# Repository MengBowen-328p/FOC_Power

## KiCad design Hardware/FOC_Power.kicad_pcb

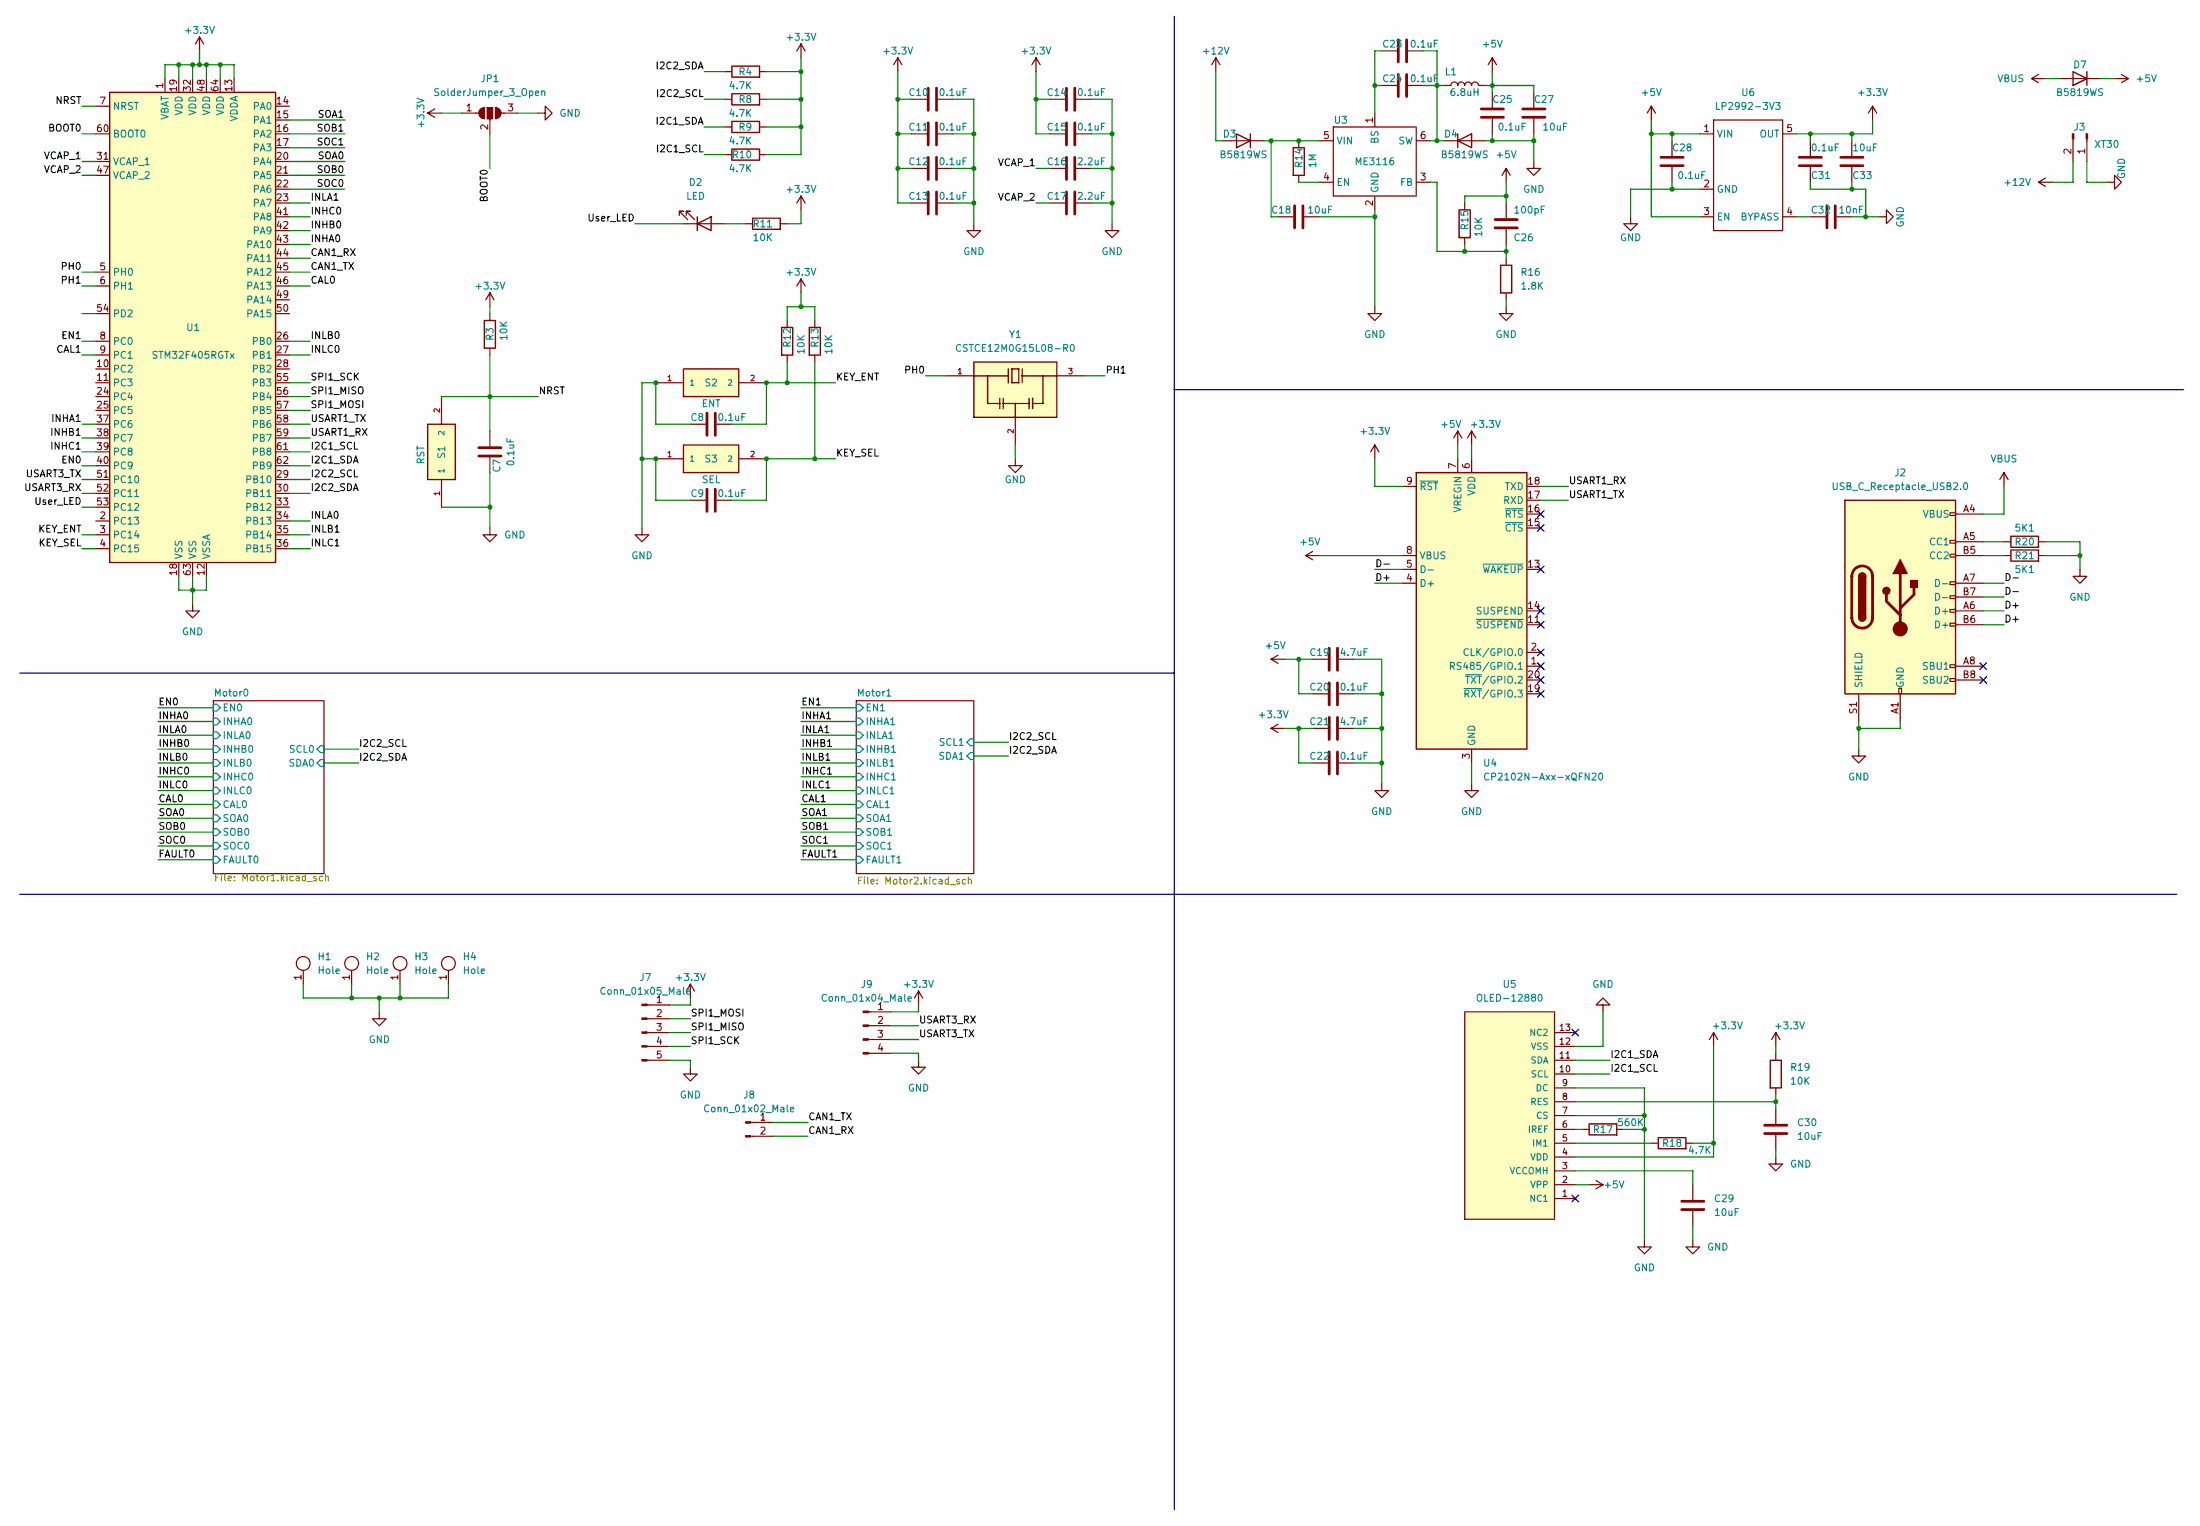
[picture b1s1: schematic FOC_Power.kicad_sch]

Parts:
C7, C8, C9, C10, C11, C12, C13, C14, C15, C20, C22, C23, C24, C25, C28, C31: 0.1uF; C_0402_1005Metric
C16, C17: 2.2uF; C_0402_1005Metric
C18, C27, C29, C30, C33: 10uF; C_0402_1005Metric
C19, C21: 4.7uF; C_0402_1005Metric
C26: 100pF; C_0402_1005Metric
C32: 10nF; C_0402_1005Metric
D2: LED; LED_0402_1005Metric
D3, D4, D7: B5819WS; D_SOD-323
H1, H2, H3, H4: Hole
J2: USB_C_Receptacle_USB2.0; USB_C_Receptacle_Palconn_UTC16-G
J3: XT30; XT30_SMD
J7: Conn_01x05_Male; JST_SUR_SM05B-SURS-TF_1x05-1MP_P0.80mm_Horizontal
J8: Conn_01x02_Male; JST_SUR_SM02B-SURS-TF_1x02-1MP_P0.80mm_Horizontal
J9: Conn_01x04_Male; JST_SUR_SM04B-SURS-TF_1x04-1MP_P0.80mm_Horizontal
JP1: SolderJumper_3_Open; SolderJumper-3_P1.3mm_Open_RoundedPad1.0x1.5mm
L1: 6.8uH; L_0805_2012Metric
R3, R11, R12, R13, R15, R19: 10K; R_0402_1005Metric
R4, R8, R9, R10, R18: 4.7K; R_0402_1005Metric
R14: 1M; R_0402_1005Metric
R16: 1.8K; R_0402_1005Metric
R17: 560K; R_0402_1005Metric
R20, R21: 5K1; R_0402_1005Metric
S1: RST; SKRK; Manufacturer_Part_Number SKRKAEE010
S2: ENT; SKRK; Manufacturer_Part_Number SKRKAEE010
S3: SEL; SKRK; Manufacturer_Part_Number SKRKAEE010
U1: STM32F405RGTx; LQFP-64_10x10mm_P0.5mm
U3: ME3116; SOT-23-6
U4: CP2102N-Axx-xQFN20; SiliconLabs_QFN-20-1EP_3x3mm_P0.5mm_EP1.8x1.8mm
U5: OLED-12880
U6: LP2992-3V3; SOT-23-5
Y1: CSTCE12M0G15L08-R0; OSC_CSTCE12M0G15L08-R0; PARTREV May 7, 2019

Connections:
+3V3: C10.2, C11.2, C12.2, C13.2, C14.2, C15.2, C21.1, C22.1, C31.1, C33.1, J7.1, J9.1, JP1.1 (A), R3.1, R4.2, R8.2, R9.2, R10.2, R11.2, R12.1, R13.1, R18.2, R19.1, U1.1 (VBAT), U1.13 (VDDA), U1.19 (VDD), U1.32 (VDD), U1.48 (VDD), U1.64 (VDD), U4.6 (VDD), U4.9 (~RST), U5.4 (VDD), U6.5 (OUT); also elsewhere on the board
+5V: C19.1, C20.1, C25.2, C26.1, C27.2, C28.2, D7.1 (K), L1.2, R15.1, U4.7 (VREGIN), U4.8 (VBUS), U5.2 (VPP), U6.1 (VIN), U6.3 (EN)
+12V: D3.2 (A), J3.2; also elsewhere on the board
/BOOT0: JP1.2 (C), U1.60 (BOOT0)
/CAL0: U1.46 (PA13); also elsewhere on the board
/CAL1: U1.9 (PC1); also elsewhere on the board
/CAN1_RX: J8.2, U1.44 (PA11)
/CAN1_TX: J8.1, U1.45 (PA12)
/D+: J2.A6 (D+), J2.B6 (D+), U4.4 (D+)
/D-: J2.A7 (D-), J2.B7 (D-), U4.5 (D-)
/EN0: U1.40 (PC9); also elsewhere on the board
/EN1: U1.8 (PC0); also elsewhere on the board
/I2C1_SCL: R10.1, U1.61 (PB8), U5.10 (SCL)
/I2C1_SDA: R9.1, U1.62 (PB9), U5.11 (SDA)
/I2C2_SCL: R8.1, U1.29 (PB10); also elsewhere on the board
/I2C2_SDA: R4.1, U1.30 (PB11); also elsewhere on the board
/INHA0: U1.43 (PA10); also elsewhere on the board
/INHA1: U1.37 (PC6); also elsewhere on the board
/INHB0: U1.42 (PA9); also elsewhere on the board
/INHB1: U1.38 (PC7); also elsewhere on the board
/INHC0: U1.41 (PA8); also elsewhere on the board
/INHC1: U1.39 (PC8); also elsewhere on the board
/INLA0: U1.34 (PB13); also elsewhere on the board
/INLA1: U1.23 (PA7); also elsewhere on the board
/INLB0: U1.26 (PB0); also elsewhere on the board
/INLB1: U1.35 (PB14); also elsewhere on the board
/INLC0: U1.27 (PB1); also elsewhere on the board
/INLC1: U1.36 (PB15); also elsewhere on the board
/KEY_ENT: C8.1, R12.2, S2.2, U1.3 (PC14); also elsewhere on the board
/KEY_SEL: C9.1, R13.2, S3.2, U1.4 (PC15)
/NRST: C7.1, R3.2, S1.2, U1.7 (NRST)
/PH0: U1.5 (PH0), Y1.1
/PH1: U1.6 (PH1), Y1.3
/SOA0: U1.20 (PA4); also elsewhere on the board
/SOA1: U1.15 (PA1); also elsewhere on the board
/SOB0: U1.21 (PA5); also elsewhere on the board
/SOB1: U1.16 (PA2); also elsewhere on the board
/SOC0: U1.22 (PA6); also elsewhere on the board
/SOC1: U1.17 (PA3); also elsewhere on the board
/SPI1_MISO: J7.3, U1.56 (PB4)
/SPI1_MOSI: J7.2, U1.57 (PB5)
/SPI1_SCK: J7.4, U1.55 (PB3)
/USART1_RX: U1.59 (PB7), U4.18 (TXD)
/USART1_TX: U1.58 (PB6), U4.17 (RXD)
/USART3_RX: J9.2, U1.52 (PC11)
/USART3_TX: J9.3, U1.51 (PC10)
/User_LED: D2.1 (K), U1.53 (PC12)
/VCAP_1: C16.2, U1.31 (VCAP_1)
/VCAP_2: C17.2, U1.47 (VCAP_2)
GND: C7.2, C8.2, C9.2, C10.1, C11.1, C12.1, C13.1, C14.1, C15.1, C16.1, C17.1, C18.2, C19.2, C20.2, C21.2, C22.2, C25.1, C27.1, C28.1, C29.2, C30.2, C31.2, C32.1, C33.2, D4.2 (A), H1.1, H2.1, H3.1, H4.1, J2.A1 (GND), J2.A12 (GND), J2.B1 (GND), J2.B12 (GND), J2.S1 (SHIELD), J3.1, J7.5, J7.MP, J8.MP, J9.4, J9.MP, JP1.3 (B), R16.2, R17.2, R20.2, R21.2, S1.1, S2.1, S3.1, U1.12 (VSSA), U1.18 (VSS), U1.63 (VSS), U3.2 (GND), U4.3 (GND), U4.12 (GND), U4.21 (GND), U5.7 (CS), U5.9 (DC), U5.12 (VSS), U6.2 (GND), Y1.2; also elsewhere on the board
unnamed: C18.1, D3.1 (K), R14.1, U3.5 (VIN)
unnamed: C23.1, C24.1, D4.1 (K), L1.1, U3.6 (SW)
unnamed: C23.2, C24.2, U3.1 (BS)
unnamed: C26.2, R15.2, R16.1, U3.3 (FB)
unnamed: C29.1, U5.3 (VCCOMH)
unnamed: C30.1, R19.2, U5.8 (RES)
unnamed: C32.2, U6.4 (BYPASS)
unnamed: D2.2 (A), R11.1
unnamed: J2.A5 (CC1), R20.1
unnamed: J2.B5 (CC2), R21.1
unnamed: R14.2, U3.4 (EN)
unnamed: R17.1, U5.6 (IREF)
unnamed: R18.1, U5.5 (IM1)
VBUS: D7.2 (A), J2.A4 (VBUS), J2.A9 (VBUS), J2.B4 (VBUS), J2.B9 (VBUS)

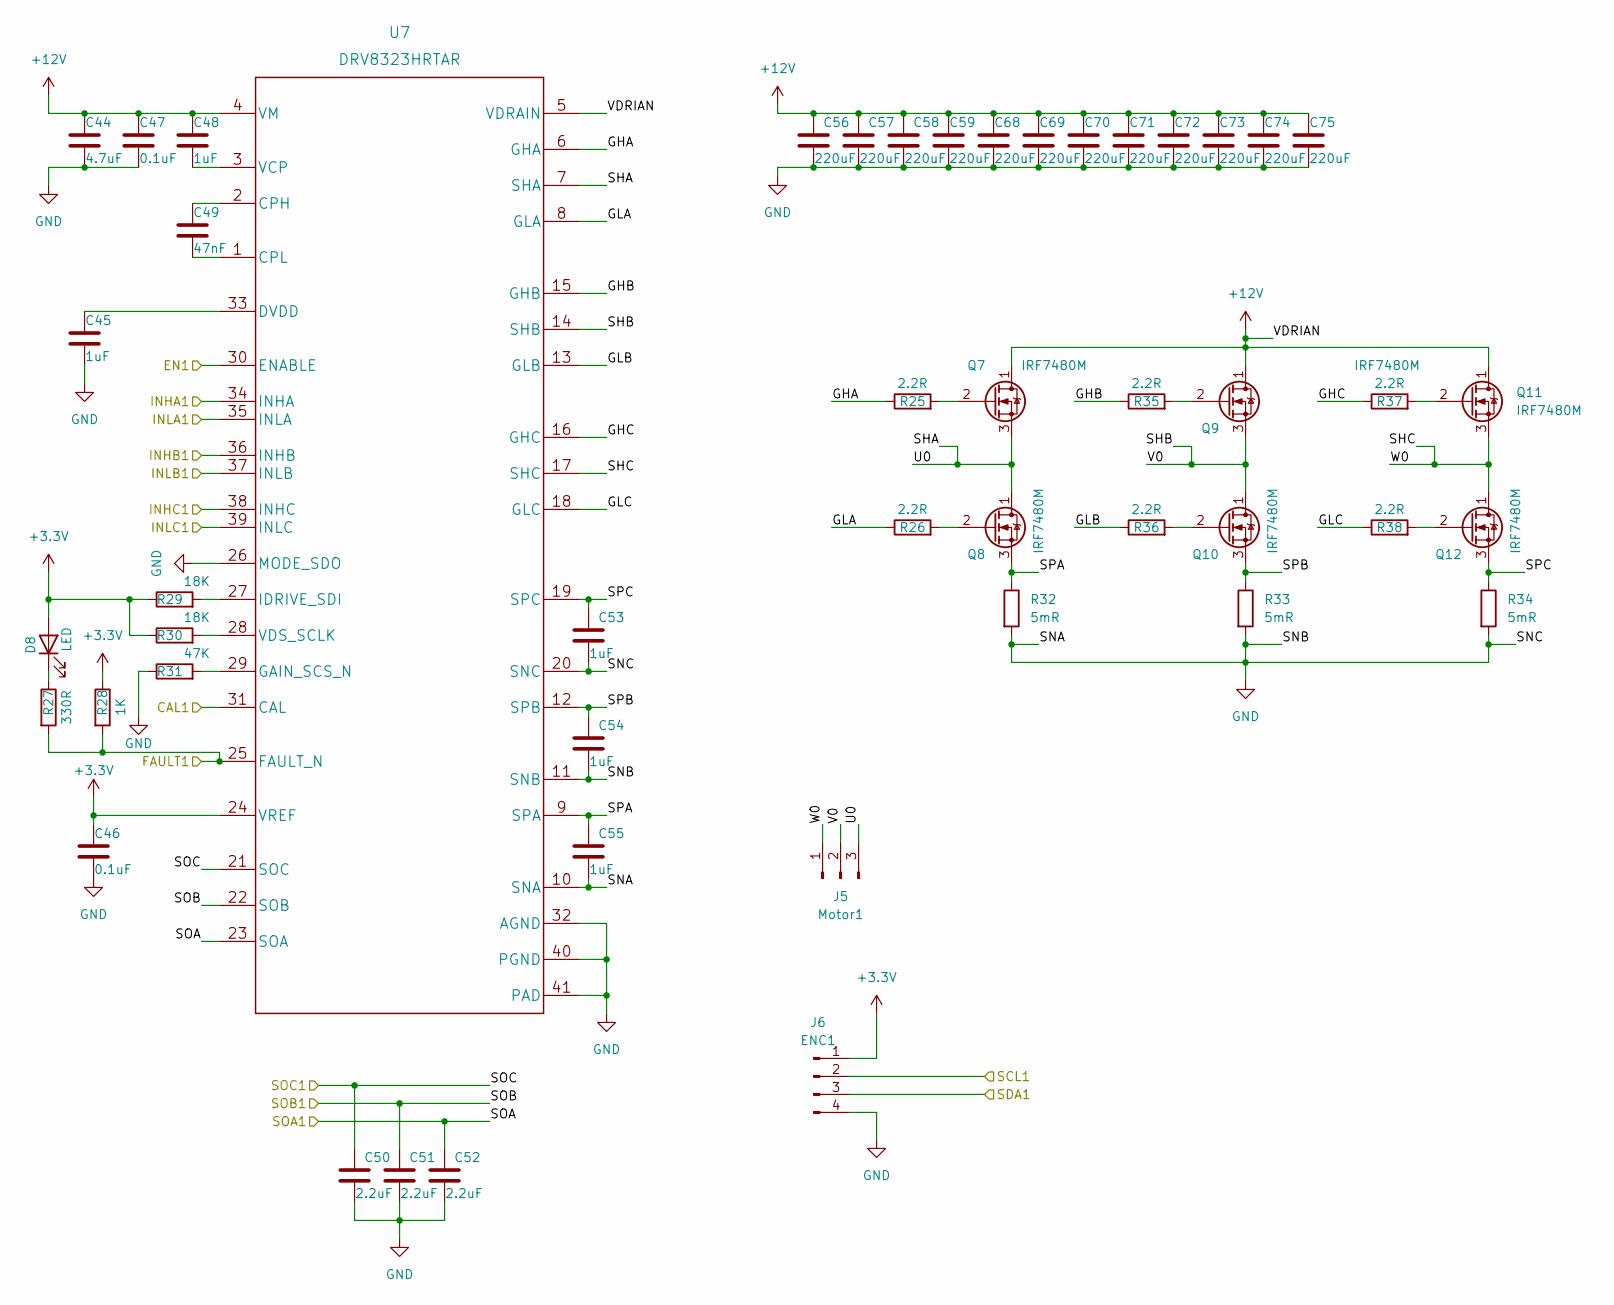
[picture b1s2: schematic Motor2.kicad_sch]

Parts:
C44: 4.7uF; C_0402_1005Metric
C45, C48: 1uF; C_0402_1005Metric
C46, C47: 0.1uF; C_0402_1005Metric
C49: 47nF; C_0402_1005Metric
C50, C51, C52: 2.2uF; C_0402_1005Metric
C53, C54, C55: 1uF; C_0603_1608Metric
C56, C57, C58, C59, C68, C69, C70, C71, C72, C73, C74, C75: 220uF; C_0805_2012Metric
D8: LED; LED_0402_1005Metric
J5: Motor1; MR30_SMD
J6: ENC1; JST_SUR_SM04B-SURS-TF_1x04-1MP_P0.80mm_Horizontal
Q7, Q8, Q9, Q10, Q11, Q12: IRF7480M; DirectFET_ME
R25, R26, R35, R36, R37, R38: 2.2R; R_0402_1005Metric
R27: 330R; R_0402_1005Metric
R28: 1K; R_0402_1005Metric
R29, R30: 18K; R_0402_1005Metric
R31: 47K; R_0402_1005Metric
R32, R33, R34: 5mR; R_2512_6332Metric
U7: DRV8323HRTAR

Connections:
+3V3: C46.1, D8.2 (A), J6.1, R28.1, R29.1, R30.1, U7.24 (VREF); also elsewhere on the board
+12V: C44.1, C47.1, C48.1, C56.1, C57.1, C58.1, C59.1, C68.1, C69.1, C70.1, C71.1, C72.1, C73.1, C74.1, C75.1, Q7.1 (D), Q9.1 (D), Q11.1 (D), U7.4 (VM), U7.5 (VDRAIN); also elsewhere on the board
/CAL1: U7.31 (CAL); also elsewhere on the board
/EN1: U7.30 (ENABLE); also elsewhere on the board
/FAULT1: R27.2, R28.2, U7.25 (FAULT_N)
/INHA1: U7.34 (INHA); also elsewhere on the board
/INHB1: U7.36 (INHB); also elsewhere on the board
/INHC1: U7.38 (INHC); also elsewhere on the board
/INLA1: U7.35 (INLA); also elsewhere on the board
/INLB1: U7.37 (INLB); also elsewhere on the board
/INLC1: U7.39 (INLC); also elsewhere on the board
/Motor1/GHA: R25.1, U7.6 (GHA)
/Motor1/GHB: R35.1, U7.15 (GHB)
/Motor1/GHC: R37.1, U7.16 (GHC)
/Motor1/GLA: R26.1, U7.8 (GLA)
/Motor1/GLB: R36.1, U7.13 (GLB)
/Motor1/GLC: R38.1, U7.18 (GLC)
/Motor1/SHA: J5.3, Q7.3 (S), Q8.1 (D), U7.7 (SHA); also elsewhere on the board
/Motor1/SHB: J5.2, Q9.3 (S), Q10.1 (D), U7.14 (SHB); also elsewhere on the board
/Motor1/SHC: J5.1, Q11.3 (S), Q12.1 (D), U7.17 (SHC); also elsewhere on the board
/Motor1/SPA: C55.1, Q8.3 (S), R32.1, U7.9 (SPA)
/Motor1/SPB: C54.1, Q10.3 (S), R33.1, U7.12 (SPB)
/Motor1/SPC: C53.1, Q12.3 (S), R34.1, U7.19 (SPC)
/SOA1: C52.1, U7.23 (SOA); also elsewhere on the board
/SOB1: C51.1, U7.22 (SOB); also elsewhere on the board
/SOC1: C50.1, U7.21 (SOC); also elsewhere on the board
GND: C44.2, C45.2, C46.2, C47.2, C50.2, C51.2, C52.2, C53.2, C54.2, C55.2, C56.2, C57.2, C58.2, C59.2, C68.2, C69.2, C70.2, C71.2, C72.2, C73.2, C74.2, C75.2, J6.4, R31.1, R32.2, R33.2, R34.2, U7.10 (SNA), U7.11 (SNB), U7.20 (SNC), U7.26 (MODE_SDO), U7.32 (AGND), U7.40 (PGND), U7.41 (PAD), U7.V; also elsewhere on the board
unnamed: C45.1, U7.33 (DVDD)
unnamed: C48.2, U7.3 (VCP)
unnamed: C49.1, U7.2 (CPH)
unnamed: C49.2, U7.1 (CPL)
unnamed: D8.1 (K), R27.1
unnamed: Q7.2 (G), R25.2
unnamed: Q8.2 (G), R26.2
unnamed: Q9.2 (G), R35.2
unnamed: Q10.2 (G), R36.2
unnamed: Q11.2 (G), R37.2
unnamed: Q12.2 (G), R38.2
unnamed: R29.2, U7.27 (IDRIVE_SDI)
unnamed: R30.2, U7.28 (VDS_SCLK)
unnamed: R31.2, U7.29 (GAIN_SCS_N)

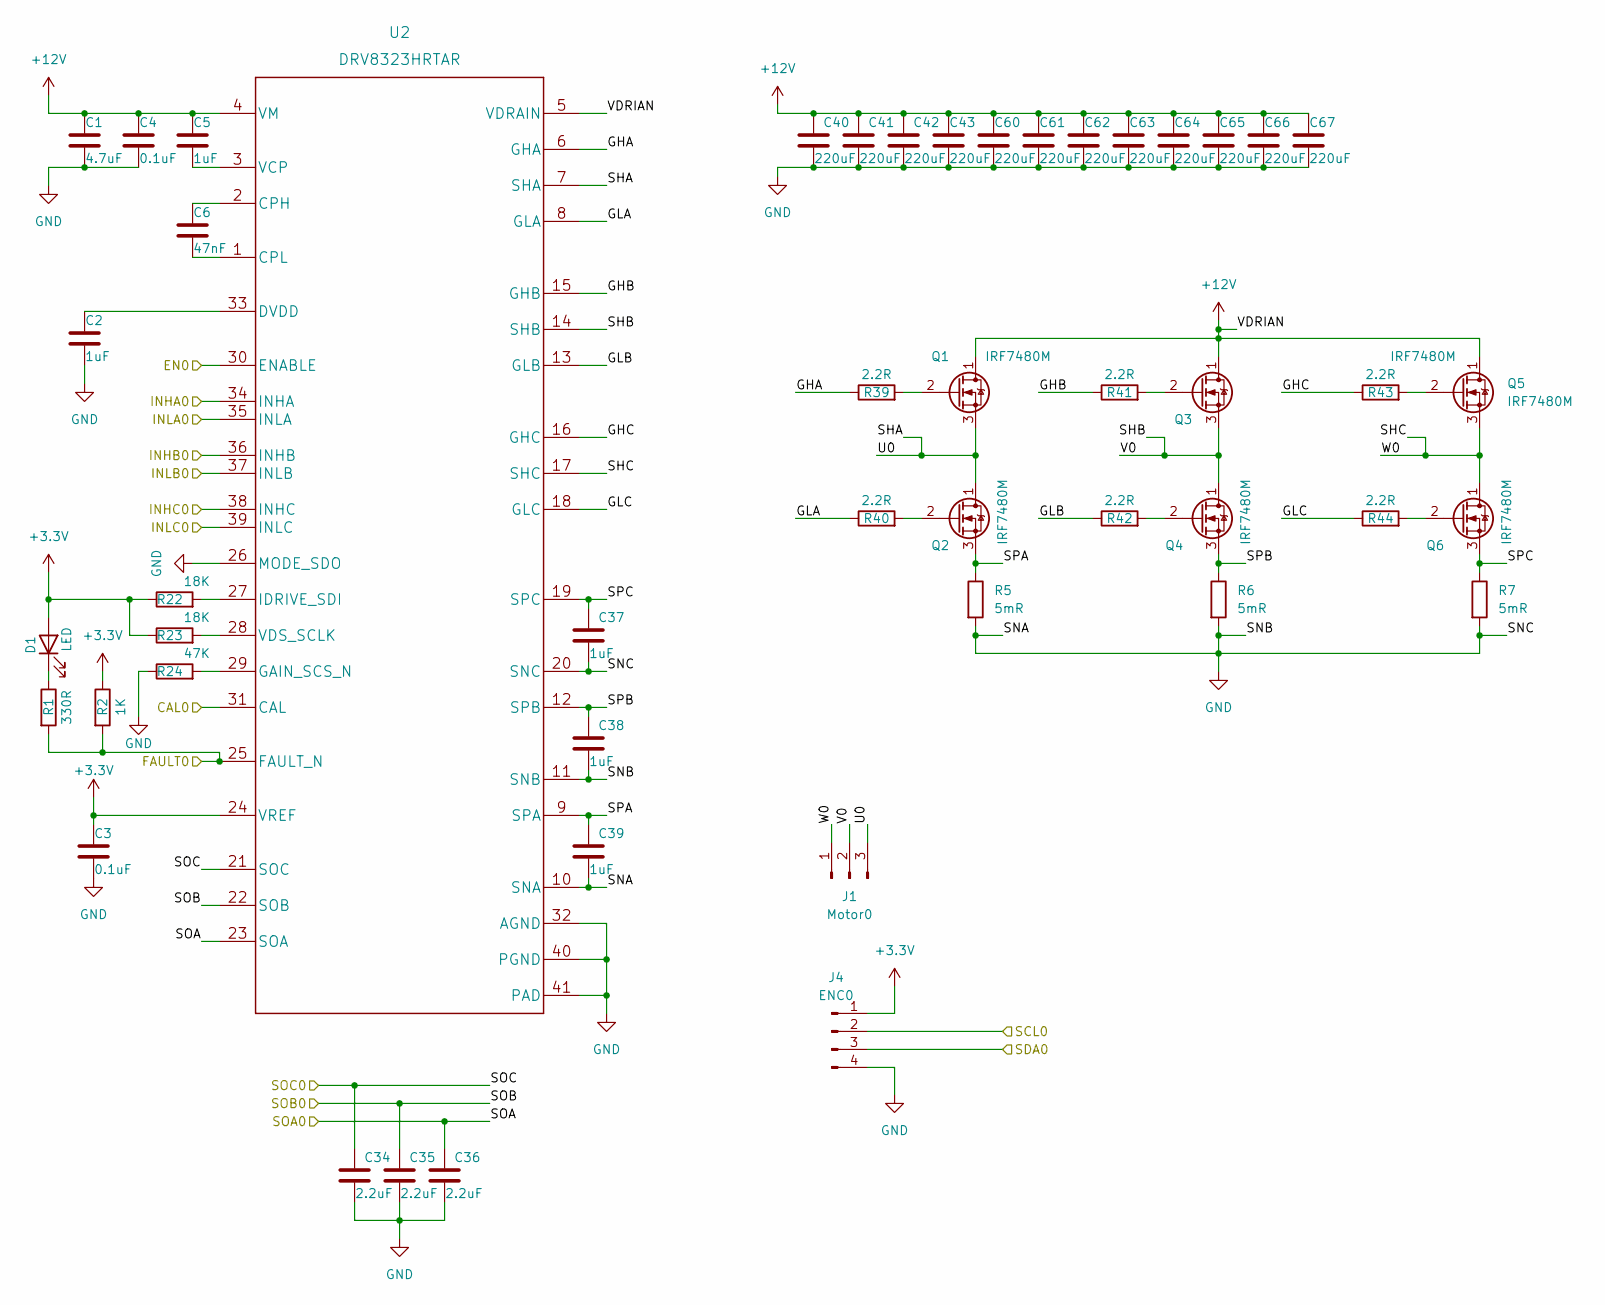
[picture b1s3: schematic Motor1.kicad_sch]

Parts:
C1: 4.7uF; C_0402_1005Metric
C2, C5: 1uF; C_0402_1005Metric
C3, C4: 0.1uF; C_0402_1005Metric
C6: 47nF; C_0402_1005Metric
C34, C35, C36: 2.2uF; C_0402_1005Metric
C37, C38, C39: 1uF; C_0603_1608Metric
C40, C41, C42, C43, C60, C61, C62, C63, C64, C65, C66, C67: 220uF; C_0805_2012Metric
D1: LED; LED_0402_1005Metric
J1: Motor0; MR30_SMD
J4: ENC0; JST_SUR_SM04B-SURS-TF_1x04-1MP_P0.80mm_Horizontal
Q1, Q2, Q3, Q4, Q5, Q6: IRF7480M; DirectFET_ME
R1: 330R; R_0402_1005Metric
R2: 1K; R_0402_1005Metric
R5, R6, R7: 5mR; R_2512_6332Metric
R22, R23: 18K; R_0402_1005Metric
R24: 47K; R_0402_1005Metric
R39, R40, R41, R42, R43, R44: 2.2R; R_0402_1005Metric
U2: DRV8323HRTAR

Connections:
+3V3: C3.1, D1.2 (A), J4.1, R2.1, R22.1, R23.1, U2.24 (VREF); also elsewhere on the board
+12V: C1.1, C4.1, C5.1, C40.1, C41.1, C42.1, C43.1, C60.1, C61.1, C62.1, C63.1, C64.1, C65.1, C66.1, C67.1, Q1.1 (D), Q3.1 (D), Q5.1 (D), U2.4 (VM), U2.5 (VDRAIN); also elsewhere on the board
/CAL0: U2.31 (CAL); also elsewhere on the board
/EN0: U2.30 (ENABLE); also elsewhere on the board
/FAULT0: R1.2, R2.2, U2.25 (FAULT_N)
/INHA0: U2.34 (INHA); also elsewhere on the board
/INHB0: U2.36 (INHB); also elsewhere on the board
/INHC0: U2.38 (INHC); also elsewhere on the board
/INLA0: U2.35 (INLA); also elsewhere on the board
/INLB0: U2.37 (INLB); also elsewhere on the board
/INLC0: U2.39 (INLC); also elsewhere on the board
/Motor0/GHA: R39.1, U2.6 (GHA)
/Motor0/GHB: R41.1, U2.15 (GHB)
/Motor0/GHC: R43.1, U2.16 (GHC)
/Motor0/GLA: R40.1, U2.8 (GLA)
/Motor0/GLB: R42.1, U2.13 (GLB)
/Motor0/GLC: R44.1, U2.18 (GLC)
/Motor0/SHA: J1.3, Q1.3 (S), Q2.1 (D), U2.7 (SHA)
/Motor0/SHB: J1.2, Q3.3 (S), Q4.1 (D), U2.14 (SHB)
/Motor0/SHC: J1.1, Q5.3 (S), Q6.1 (D), U2.17 (SHC)
/Motor0/SPA: C39.1, Q2.3 (S), R5.1, U2.9 (SPA)
/Motor0/SPB: C38.1, Q4.3 (S), R6.1, U2.12 (SPB)
/Motor0/SPC: C37.1, Q6.3 (S), R7.1, U2.19 (SPC)
/SOA0: C36.1, U2.23 (SOA); also elsewhere on the board
/SOB0: C35.1, U2.22 (SOB); also elsewhere on the board
/SOC0: C34.1, U2.21 (SOC); also elsewhere on the board
GND: C1.2, C2.2, C3.2, C4.2, C34.2, C35.2, C36.2, C37.2, C38.2, C39.2, C40.2, C41.2, C42.2, C43.2, C60.2, C61.2, C62.2, C63.2, C64.2, C65.2, C66.2, C67.2, J4.4, R5.2, R6.2, R7.2, R24.1, U2.10 (SNA), U2.11 (SNB), U2.20 (SNC), U2.26 (MODE_SDO), U2.32 (AGND), U2.40 (PGND), U2.41 (PAD), U2.V; also elsewhere on the board
unnamed: C2.1, U2.33 (DVDD)
unnamed: C5.2, U2.3 (VCP)
unnamed: C6.1, U2.2 (CPH)
unnamed: C6.2, U2.1 (CPL)
unnamed: D1.1 (K), R1.1
unnamed: Q1.2 (G), R39.2
unnamed: Q2.2 (G), R40.2
unnamed: Q3.2 (G), R41.2
unnamed: Q4.2 (G), R42.2
unnamed: Q5.2 (G), R43.2
unnamed: Q6.2 (G), R44.2
unnamed: R22.2, U2.27 (IDRIVE_SDI)
unnamed: R23.2, U2.28 (VDS_SCLK)
unnamed: R24.2, U2.29 (GAIN_SCS_N)

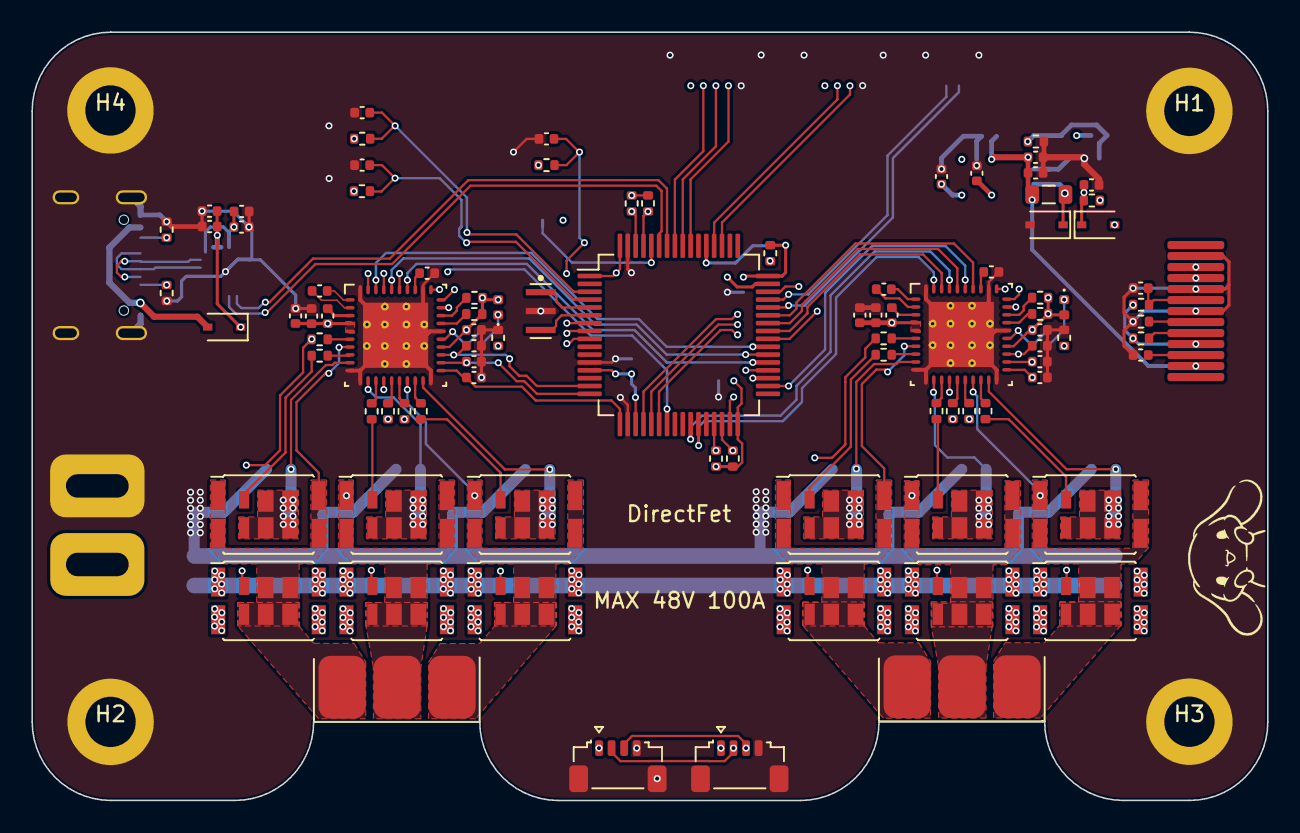
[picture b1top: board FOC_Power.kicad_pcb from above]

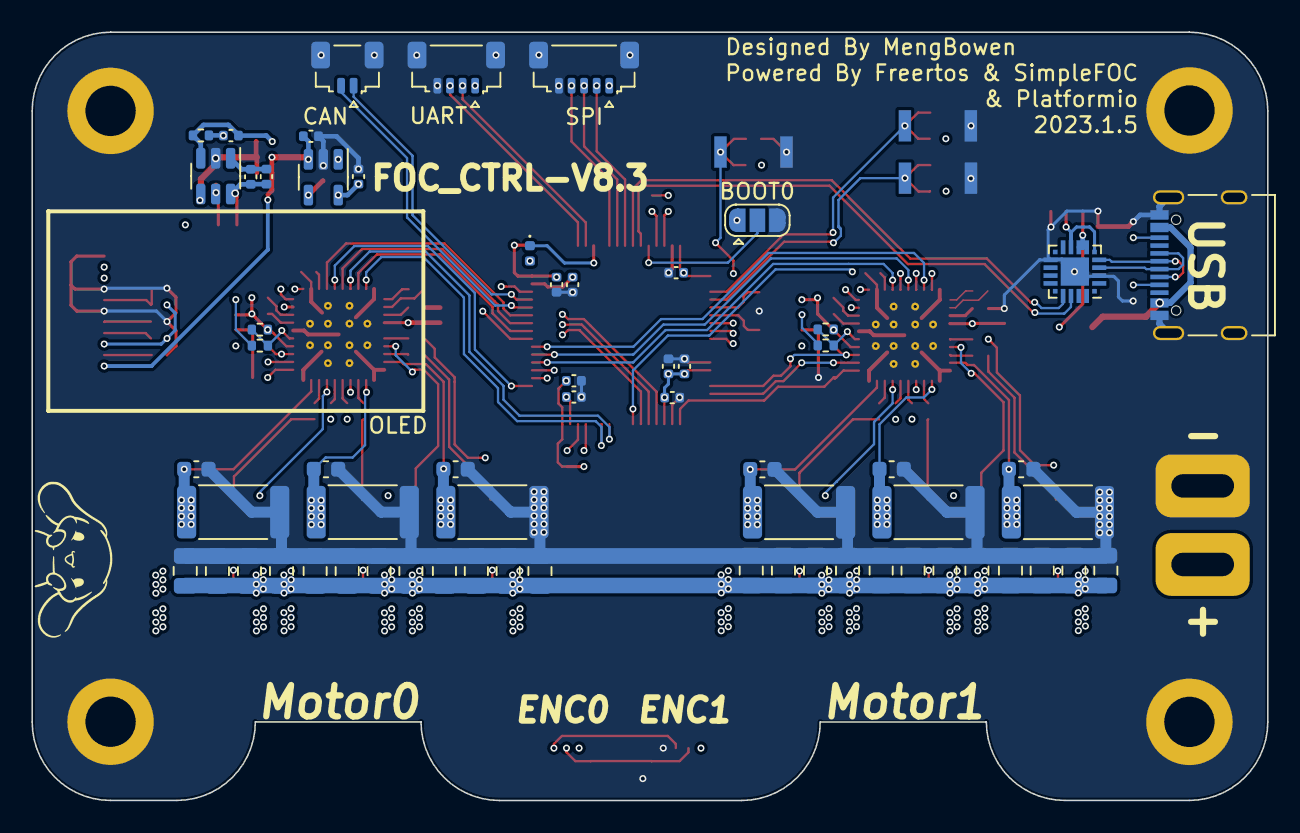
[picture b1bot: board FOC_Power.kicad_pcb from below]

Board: 4 copper layers, 78.7 x 48.9 mm, 163 parts (66 on the bottom side), 118 nets.

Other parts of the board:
ENC0: ENC0; JST_SUR_SM04B-SURS-TF_1x04-1MP_P0.80mm_Horizontal
ENC1: ENC1; JST_SUR_SM04B-SURS-TF_1x04-1MP_P0.80mm_Horizontal
MOTOR1: Motor1; MR30_SMD
S: ENT; SKRK

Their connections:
+3V3: ENC0.1, ENC1.1; also elsewhere on the board
/I2C2_SCL: ENC0.2, ENC1.2; also elsewhere on the board
/I2C2_SDA: ENC0.3, ENC1.3; also elsewhere on the board
/KEY_ENT: S.2; also elsewhere on the board
/Motor1/SHA: MOTOR1.3; also elsewhere on the board
/Motor1/SHB: MOTOR1.2; also elsewhere on the board
/Motor1/SHC: MOTOR1.1; also elsewhere on the board
GND: ENC0.4, ENC0.MP, ENC1.4, ENC1.MP, S.1; also elsewhere on the board

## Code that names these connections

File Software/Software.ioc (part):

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Mcu.Name=STM32F405RGTx
Mcu.Package=LQFP64
Mcu.UserName=STM32F405RGTx
PA1.Signal=ADCx_IN1
PA10.Signal=S_TIM1_CH3
PA11.Mode=CAN_Activate
PA11.Signal=CAN1_RX
PA12.Mode=CAN_Activate
PA12.Signal=CAN1_TX
PA13.Mode=Serial_Wire
PA13.Signal=SYS_JTMS-SWDIO
PA14.Mode=Serial_Wire
PA14.Signal=SYS_JTCK-SWCLK
PA15.GPIOParameters=GPIO_Label
PA15.GPIO_Label=CAL0
PA15.Signal=GPIO_Output
PA2.Signal=ADCx_IN2
PA3.Signal=ADCx_IN3
PA4.Signal=ADCx_IN4
PA5.Signal=ADCx_IN5
PA6.Signal=ADCx_IN6
PA7.Mode=PWM Generation1 CH1 CH1N
PA7.Signal=TIM8_CH1N
PA8.Signal=S_TIM1_CH1
PA9.Signal=S_TIM1_CH2
PB0.Mode=Output Compare2 CH2 CH2N
PB0.Signal=TIM1_CH2N
PB1.Mode=Output Compare3 CH3 CH3N
PB1.Signal=TIM1_CH3N
PB10.Mode=I2C
PB10.Signal=I2C2_SCL
PB11.Mode=I2C
PB11.Signal=I2C2_SDA
PB13.Mode=Output Compare1 CH1 CH1N
PB13.Signal=TIM1_CH1N
PB14.Mode=PWM Generation2 CH2 CH2N
PB14.Signal=TIM8_CH2N
PB15.Mode=Output Compare3 CH3 CH3N
PB15.Signal=TIM8_CH3N
PB3.Mode=Full_Duplex_Master
PB3.Signal=SPI1_SCK
PB4.Mode=Full_Duplex_Master
PB4.Signal=SPI1_MISO
PB5.Mode=Full_Duplex_Master
PB5.Signal=SPI1_MOSI
PB6.Mode=Asynchronous
PB6.Signal=USART1_TX
PB7.Mode=Asynchronous
PB7.Signal=USART1_RX
PB8.Mode=I2C
PB8.Signal=I2C1_SCL
PB9.Mode=I2C
PB9.Signal=I2C1_SDA
PC0.GPIOParameters=GPIO_Label
PC0.GPIO_Label=EN1
PC0.Signal=GPIO_Output
PC1.GPIOParameters=GPIO_Label
PC1.GPIO_Label=CAL1
PC1.Signal=GPIO_Output
PC10.Mode=Asynchronous
PC10.Signal=USART3_TX
PC11.Mode=Asynchronous
PC11.Signal=USART3_RX
PC14-OSC32_IN.GPIOParameters=GPIO_Label
PC14-OSC32_IN.GPIO_Label=ENT
PC14-OSC32_IN.Signal=GPIO_Input
PC15-OSC32_OUT.GPIOParameters=GPIO_Label
PC15-OSC32_OUT.GPIO_Label=SEL
PC15-OSC32_OUT.Signal=GPIO_Input
PC6.Signal=S_TIM8_CH1
PC7.Signal=S_TIM8_CH2
PC8.Signal=S_TIM8_CH3
PC9.GPIOParameters=GPIO_Label
PC9.GPIO_Label=EN0
PC9.Signal=GPIO_Output
PD2.GPIOParameters=GPIO_Speed,GPIO_Label
PD2.GPIO_Label=User_LED
PD2.GPIO_Speed=GPIO_SPEED_FREQ_HIGH
PD2.Signal=GPIO_Output
PH0-OSC_IN.Mode=HSE-External-Oscillator
PH0-OSC_IN.Signal=RCC_OSC_IN
PH1-OSC_OUT.Mode=HSE-External-Oscillator
PH1-OSC_OUT.Signal=RCC_OSC_OUT
RCC.HSE_VALUE=25000000
RCC.SYSCLKFreq_VALUE=16000000
board=custom

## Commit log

2022-12-31 Init Files
2023-01-05 Init FreeRTOS
